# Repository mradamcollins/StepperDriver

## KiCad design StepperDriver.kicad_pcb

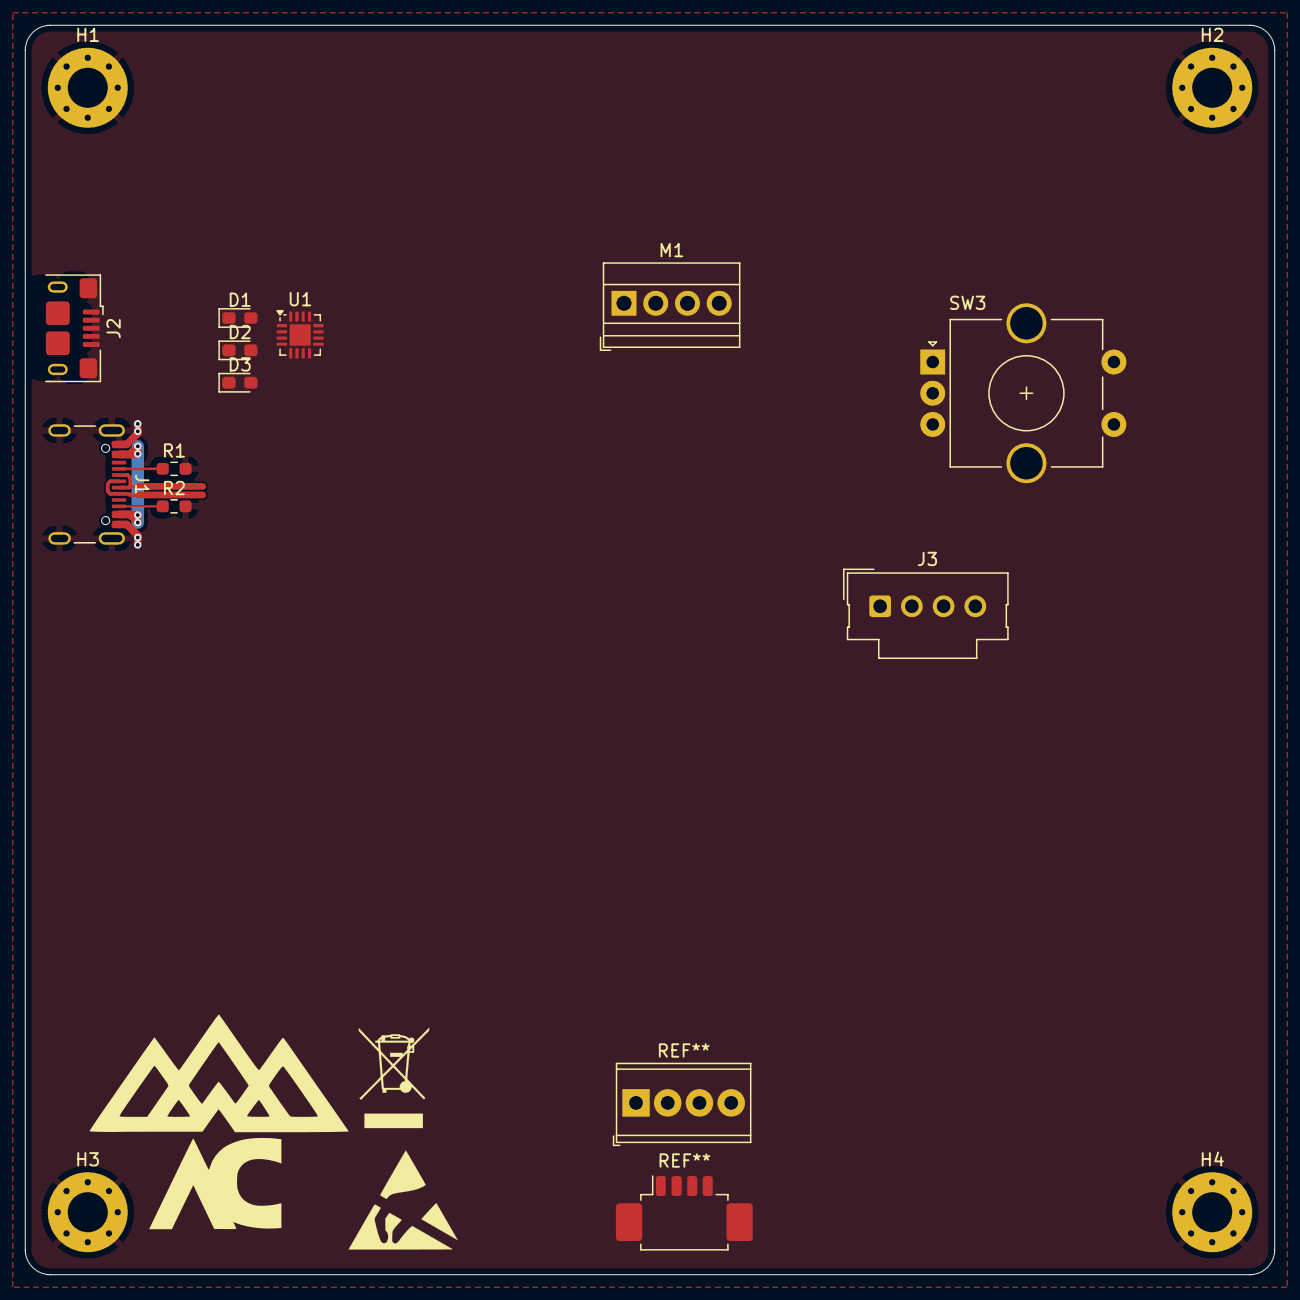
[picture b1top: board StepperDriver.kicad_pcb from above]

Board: 2 copper layers, 100.0 x 100.0 mm, 16 parts (0 on the bottom side), 6 nets.

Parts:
AC_LOGO: LOGO; AC_Logo_17mm_20mm
D1, D2, D3: LED; LED_0603_1608Metric_Pad1.05x0.95mm_HandSolder
H1, H2, H3, H4: MountingHole_Pad; MountingHole_3.2mm_M3_Pad_Via
J1: USB4105-GF-A; USB_C_Receptacle_GCT_USB4105-xx-A_16P_TopMnt_Horizontal
J2: USB_B_Micro; USB_Micro-B_Amphenol_10118193-0001LF_Horizontal
J3: Conn_01x04_Socket; Molex_SL_171971-0004_1x04_P2.54mm_Vertical
M1: Stepper_Motor_bipolar; TerminalBlock_Xinya_XY308-2.54-4P_1x04_P2.54mm_Horizontal
R1, R2: 5.1K; R_0603_1608Metric_Pad0.98x0.95mm_HandSolder
SW3: RotaryEncoder_Switch_MP; RotaryEncoder_Alps_EC11E-Switch_Vertical_H20mm_CircularMoun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
U1: STSPIN220; VQFN-16-1EP_3x3mm_P0.5mm_EP1.68x1.68mm

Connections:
/USB+: J1.A6 (D+), J1.B6 (D+)
/USB-: J1.A7 (D-), J1.B7 (D-)
GND: H1.1, H2.1, H3.1, H4.1, J1.A1 (GND), J1.A12 (GND), J1.B1 (GND), J1.B12 (GND), J1.S1 (SHIELD), R1.2, R2.2
unnamed: J1.A5 (CC1), R1.1
unnamed: J1.B5 (CC2), R2.1
VBUS: J1.A4 (VBUS), J1.A9 (VBUS), J1.B4 (VBUS), J1.B9 (VBUS)

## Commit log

2024-11-15 initial commit adding AC-kicad-library as submodule
2024-11-15 Initial commit adding library
2024-11-15 Removed backups, added .igitignore
2024-11-15 Modified library tables
2024-11-15 updating submodule
2024-11-15 update git ignore
2024-11-15 removed cache
2024-11-15 Updated Logo library reference
2024-11-26 update schematic image
2024-11-26 new library updates
2024-12-04 Update library submodule
